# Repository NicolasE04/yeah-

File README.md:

Student Name: Nicolas Evangelista
Student #:5007797790
Student Email: evangn1@unlv.nevada.edu

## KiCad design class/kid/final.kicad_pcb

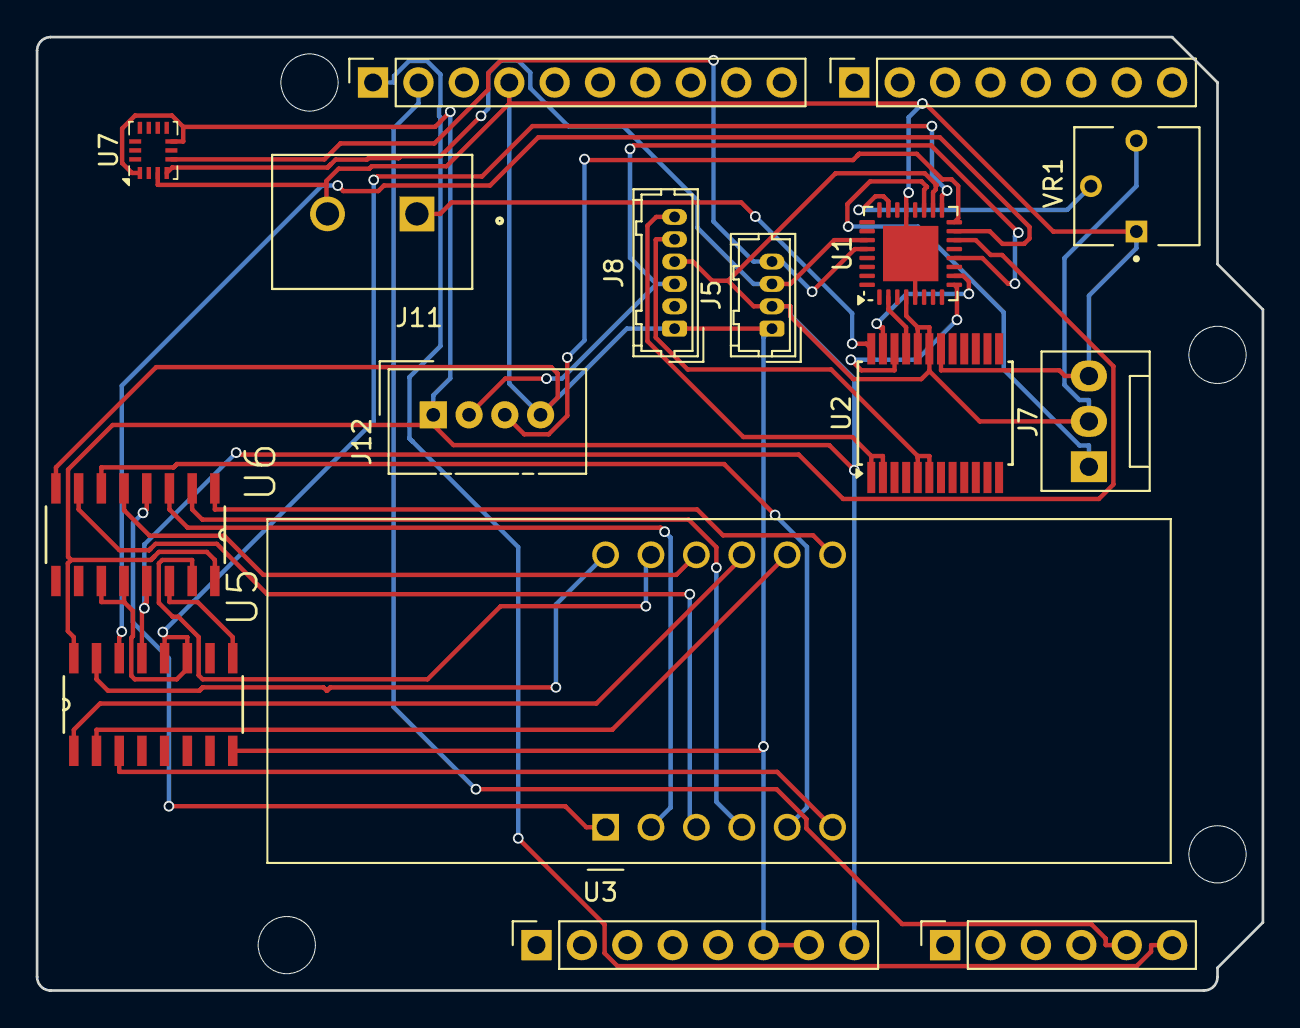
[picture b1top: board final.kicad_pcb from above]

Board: 2 copper layers, 68.6 x 53.3 mm, 20 parts (0 on the bottom side), 32 nets.

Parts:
J1: Power; PinSocket_1x08_P2.54mm_Vertical
J2: Digital/PWM; PinSocket_1x10_P2.54mm_Vertical
J3: Analog; PinSocket_1x06_P2.54mm_Vertical
J4: Digital/PWM; PinSocket_1x08_P2.54mm_Vertical
J5: Conn_01x04_Pin_oled; Hirose_DF13-04P-1.25DSA_1x04_P1.25mm_Vertical
J7: Conn_01x03_Pin_servo; FanPinHeader_1x03_P2.54mm_Vertical
J8: Conn_01x06_Pin_motor; Hirose_DF13-06P-1.25DSA_1x06_P1.25mm_Vertical
J11: OSTTC020162; OST_OSTTC020162
J12: Conn_01x04_Pin; NS-Tech_Grove_1x04_P2mm_Vertical
MH1, MH2, MH3, MH4: MountingHole_3.2mm
U1: ATmega328PB-M; QFN-32-1EP_5x5mm_P0.5mm_EP3.1x3.1mm
U2: TB6612FNG; SSOP-24_5.3x8.2mm_P0.65mm
U3: CA56-12SEKWA
U5, U6: 74HC595D_118; SOIC127P600X175-16N
U7: MY_BMI160; Bosch_LGA-14_3x2.5mm_P0.5mm
VR1: 3362P-1-103LF; TRIM_3362P-1-103LF

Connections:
/SCL/A5: J2.1, J3.6
/SDA/A4: J2.2, J3.5
GND: J1.6, J1.7, J2.4, J5.1, J7.3, J8.1, J11.2, J12.4, U1.5 (GND), U1.21 (GND), U1.33 (GND), U2.18 (GND), U5.8 (GND), U6.8 (GND), U7.3 (GND), VR1.1
unnamed: J8.5, U2.5 (AO2), U2.6 (AO2)
unnamed: J8.6, U2.1 (AO1), U2.2 (AO1)
unnamed: U1.23 (PC0), VR1.2
unnamed: U1.2 (PD4), U2.21 (AIN1)
unnamed: U1.9 (PD5), U2.22 (AIN2)
unnamed: U1.10 (PD6), U2.23 (PWMA)
unnamed: J11.1, U2.24 (VM1)
unnamed: U3.12 (CA1), U5.15 (Q0)
unnamed: U3.9 (CA2), U5.1 (Q1)
unnamed: U3.8 (CA3), U5.2 (Q2)
unnamed: U3.6 (CA4), U5.3 (Q3)
unnamed: U3.3 (DPX), U6.7 (Q7)
unnamed: U3.11 (a), U6.15 (Q0)
unnamed: U3.7 (b), U6.1 (Q1)
unnamed: U3.4 (c), U6.2 (Q2)
unnamed: U3.2 (d), U6.3 (Q3)
unnamed: U3.1 (e), U6.4 (Q4)
unnamed: U3.10 (f), U6.5 (Q5)
unnamed: U3.5 (g), U6.6 (Q6)
unnamed: U5.9 (Q7_2), U6.14 (DS)
PB0: J8.3, J12.2, U1.12 (PB0)
SCL0: J5.3, U1.27 (PC4), U7.4 (SCL)
SDA0: J5.4, U1.28 (PC5), U7.5 (SDA)
SERpin: J7.1, U1.19 (PE2)
SPICLK: U1.17 (PB5), U5.11 (SH_CP), U5.12 (ST_CP), U6.11 (SH_CP), U6.12 (ST_CP)
VCC: J1.8, J5.2, J7.2, J8.4, J12.1, U1.4 (VCC), U1.18 (AVCC), U2.19 (STBY), U2.20 (VCC), U5.16 (VCC), U6.16 (VCC), U7.1 (Vin), U7.7 (SAO), VR1.3
spiDATA: U1.15 (PB3), U5.14 (DS)
ss: U1.14 (PB2), U5.13 (~OE), U6.13 (~OE)
trig: J12.3, U1.16 (PB4)

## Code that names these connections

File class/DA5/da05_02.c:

// da5_02
// nicolas evangelista

// Task 02 Objective:
// Connect the encoder pins to Timer1 to calculate the
// init motor
#define F_CPU 16000000UL
#define BAUDRATE 57600
#define BAUD_PRESCALER (((F_CPU / (BAUDRATE * 16UL))) - 1)
#define PULSES_PER_REV 1000

#include <avr/io.h>
#include <stdlib.h>
#include <avr/interrupt.h>
#include <stdint.h>
#include <util/delay.h>

// Global variables
char buffer[5]; //Output of the itoa function
volatile uint16_t pulse_count = 0;
volatile uint16_t pulses_per_second = 0;

// init adc
void adc_init(void){
	// Prescalar = 64
	ADCSRA |= ((1 << ADPS2) | (1 << ADPS1));
	
	// Voltage reference from Avcc (5v)
	ADMUX |= (1<<REFS0);
	
	// init adc
	ADCSRA |= (1<<ADEN);
}

// Function to read a channel
// init adc
uint16_t read_adc(uint8_t channel){
	ADCSRA |= (1 << ADSC);

	while (ADCSRA & (1 << ADSC));
	return ADC;
}

unsigned char usart_receive(void) {
	while (!(UCSR0A & (1 << RXC0)));
	return UDR0;
}

void usart_transmit(char c) {

	while (! (UCSR0A & (1 << UDRE0)));
	UDR0 = c;
}

void usart_getline(char* buffer, uint8_t n) {
	uint8_t i = 0;	
	char c;			

	do {
		c = usart_receive();
		buffer[i++] = c;
	}
	while((i < n) && (c != '\r'));
	buffer[i] = 0;
}

void usart_sendstring(char *word) {
	
	while(*word != '\0') {
		usart_transmit(*word);	
		word++;					
	}
}

void usart_init() {
	// Set baud rate
	UBRR0H = (BAUD_PRESCALER >> 8);
	UBRR0L = BAUD_PRESCALER;

	// transmit
	UCSR0B = (1 << TXEN0) | (1 << RXEN0);

	// Asynchronous (00), no parity (00), 1 stop bit (0), 8-bit data (011)
	UCSR0C = (1 << UCSZ01) | (1 << UCSZ00);
}

// pwm waveform
void pwm_init(void) {
	// OC0A as output
	DDRD |= (1 << PD6);

	// init pwm
	TCCR0A = (1 << COM0A1) | (1 << WGM01) | (1 << WGM00);

	// Prescaler 64
	TCCR0B = (1 << CS01) | (1 << CS00);
}

// init motor
void motor_init(void) {
	// Determines spin direction
	DDRD |= (1 << PD4) | (1 << PD5);

	// set direction
	PORTD |= (1 << PD4);
	PORTD &= ~(1 << PD5);
}


void input_capture_init() {
	// Set PB0 input
	DDRB &= ~(1 << DDB0);

	// Normal mode
	TCCR1A = 0;

	// No prescaler (1x speed), rising edge initially
	TCCR1B = (1 << ICES1) | (1 << CS10);

	// Enable Input Capture interrupt
	TIMSK1 = (1 << ICIE1);


	// Initialize Timer1 counter
	TCNT1 = 0;

	// Enable global interrupts
	sei();
}

ISR(TIMER1_CAPT_vect) {
	pulse_count++;
}

// count pulses
void update_pulse_rate() {
	pulses_per_second = pulse_count;
	pulse_count = 0;
}

int main(void){
	adc_init();
	usart_init();
	pwm_init();
	motor_init();
	input_capture_init();

	while(1) {
		uint16_t adc_value = read_adc(0);
		uint8_t pwm_value = (adc_value * 255UL) / 1023;

		// init motor
		OCR0A = pwm_value;

		_delay_ms(1000);
		update_pulse_rate();
		
		usart_sendstring("RPM: ");

		double rpm = pulses_per_second / 2.5;
		
		itoa(rpm, buffer, 10);

		usart_sendstring(buffer);
		usart_transmit('\n');
	}
}

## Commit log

2025-02-24 README.md
2025-04-07 Create da4
2025-04-07 Rename da4 to class/da4
2025-04-15 DA 2
2025-04-15 Create DA3
2025-05-08 Create task1
2025-05-12 Create task01
2025-05-12 Create hello
2025-05-14 Create yo
